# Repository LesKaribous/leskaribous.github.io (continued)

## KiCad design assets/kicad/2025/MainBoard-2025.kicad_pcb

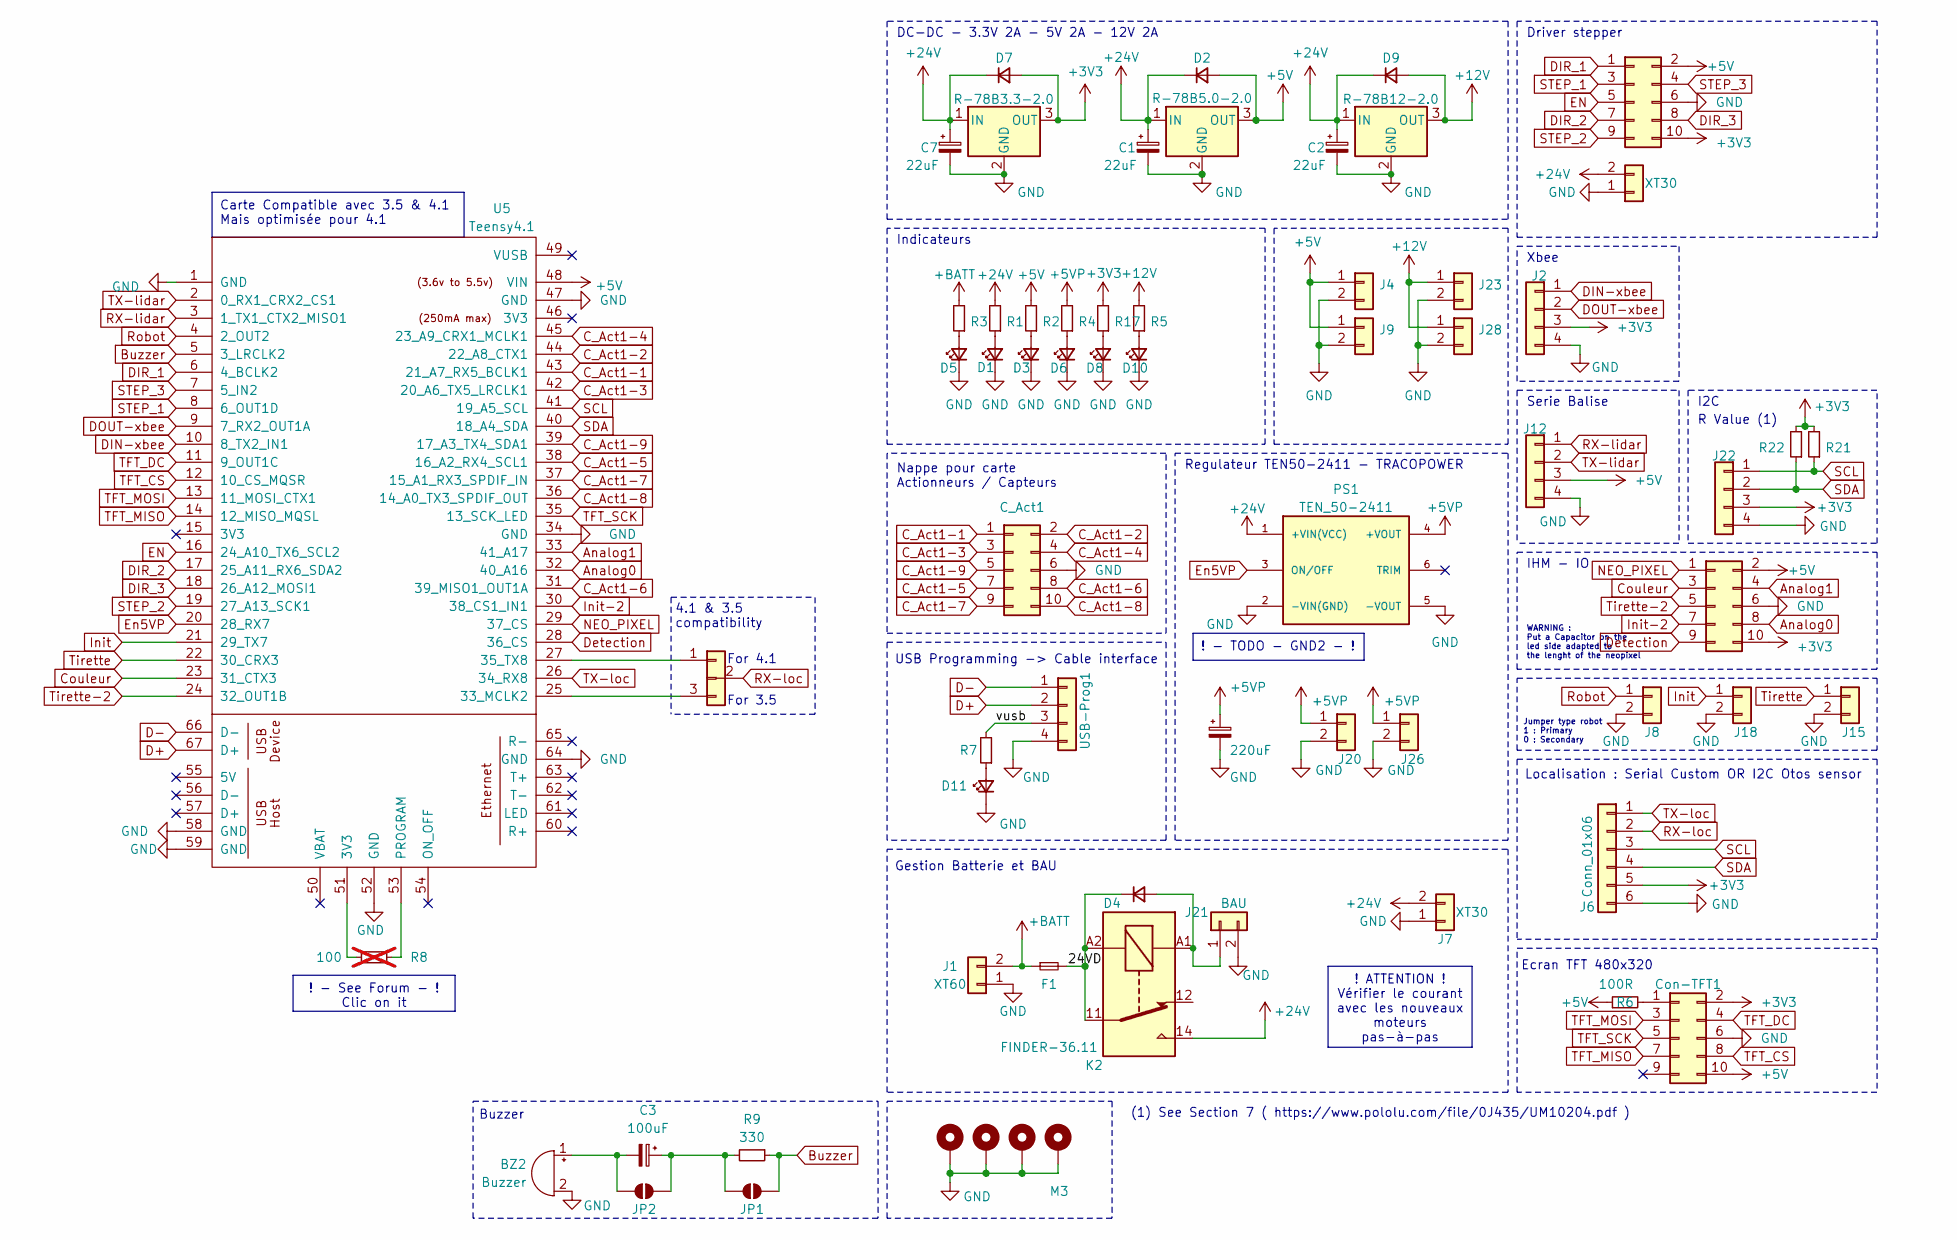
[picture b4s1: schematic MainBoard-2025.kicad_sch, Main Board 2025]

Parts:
BZ2: Buzzer; Buzzer_12x9.5RM7.6
C1, C2, C7: 22uF; CP_Elec_5x5.4
C3: 100uF; CP_Elec_5x5.4
C6: 220uF; CP_Radial_D8.0mm_P3.80mm
C_Act1: Conn_02x05_Odd_Even; IDC-Header_2x05_P2.54mm_Vertical
Con-TFT1: Conn_02x05_Odd_Even; IDC-Header_2x05_P2.54mm_Vertical
D1, D3, D5, D6, D8, D10, D11: LED_Small; LED_1206_3216Metric_Pad1.42x1.75mm_HandSolder
D2, D4, D7, D9: D_Small; D_SMA_Handsoldering
F1: Fuse_Small; Fuseholder_Blade_Mini_Keystone_3568
H1, H2, H3, H4: M3; MountingHole_3.2mm_M3_Pad_Via
IHM-IO1, IHM-IO2: Conn_02x05_Odd_Even; IDC-Header_2x05_P2.54mm_Vertical
J1: XT60; AMASS_XT60-M_1x02_P7.20mm_Vertical
J2, J12, J22: Conn_01x04; Molex_KK-254_AE-6410-04A_1x04_P2.54mm_Vertical
J3: Conn_01x03; PinHeader_1x03_P2.54mm_Vertical
J4, J9, J15, J18, J23, J28: Conn_01x02; Molex_KK-254_AE-6410-02A_1x02_P2.54mm_Vertical
J6: Conn_01x06; Molex_KK-254_AE-6410-06A_1x06_P2.54mm_Vertical
J7, J16: XT30; AMASS_XT30U-F_1x02_P5.0mm_Vertical
J8: Conn_01x02; PinHeader_1x02_P2.54mm_Vertical
J20, J21, J26: BAU; Molex_KK-396_A-41791-0002_1x02_P3.96mm_Vertical
JP1, JP2: SolderJumper_2_Open; SolderJumper-2_P1.3mm_Open_RoundedPad1.0x1.5mm
K2: FINDER-36.11; Relay_SPDT_Finder_36.11
PS1: TEN_50-2411; CONV_TEN_50-2411; PARTREV February 3, 2021
R1, R2, R3, R4, R5, R7, R17, R21, R22: R_Small; R_1206_3216Metric_Pad1.30x1.75mm_HandSolder
R6: 100R; R_1206_3216Metric_Pad1.30x1.75mm_HandSolder
R8: 100; R_1206_3216Metric_Pad1.30x1.75mm_HandSolder; not fitted
R9: 330; R_1206_3216Metric_Pad1.30x1.75mm_HandSolder
U2: R-78B3.3-2.0; Converter_DCDC_RECOM_R-78B-2.0_THT
U3: R-78B12-2.0; Converter_DCDC_RECOM_R-78B-2.0_THT
U4: R-78B5.0-2.0; Converter_DCDC_RECOM_R-78B-2.0_THT
U5: Teensy4.1; Teensy41
USB-Prog1: Conn_01x04; Molex_KK-254_AE-6410-04A_1x04_P2.54mm_Vertical

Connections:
+3V3: Con-TFT1.2, D7.2 (A), IHM-IO1.10, IHM-IO2.10, J2.3, J6.5, J22.3, R17.2, R21.2, R22.2, U2.3 (OUT)
+5V: Con-TFT1.10, D2.2 (A), IHM-IO1.2, IHM-IO2.2, J4.1, J9.1, J12.3, R2.2, R6.1, U4.3 (OUT), U5.48 (VIN)
+5VP: C6.1, J20.1, J26.1, PS1.4 (+VOUT), R4.2
+12V: D9.2 (A), J23.1, J28.1, R5.2, U3.3 (OUT)
+24V: C1.1, C2.1, C7.1, D2.1 (K), D7.1 (K), D9.1 (K), J7.2, J16.2, K2.14, PS1.1 (+VIN(VCC)), R1.2, U2.1 (IN), U3.1 (IN), U4.1 (IN)
+BATT: F1.1, J1.2, R3.2
/24VD: D4.1 (K), F1.2, K2.11, K2.A2
/vusb: R7.2, USB-Prog1.3
Analog0: IHM-IO1.8, U5.32 (40_A16)
Analog1: IHM-IO1.4, U5.33 (41_A17)
Buzzer: JP1.2 (B), R9.1, U5.5 (3_LRCLK2)
C_Act1-1: C_Act1.1, U5.43 (21_A7_RX5_BCLK1)
C_Act1-2: C_Act1.2, U5.44 (22_A8_CTX1)
C_Act1-3: C_Act1.3, U5.42 (20_A6_TX5_LRCLK1)
C_Act1-4: C_Act1.4, U5.45 (23_A9_CRX1_MCLK1)
C_Act1-5: C_Act1.7, U5.38 (16_A2_RX4_SCL1)
C_Act1-6: C_Act1.8, U5.31 (39_MISO1_OUT1A)
C_Act1-7: C_Act1.9, U5.37 (15_A1_RX3_SPDIF_IN)
C_Act1-8: C_Act1.10, U5.36 (14_A0_TX3_SPDIF_OUT)
C_Act1-9: C_Act1.5, U5.39 (17_A3_TX4_SDA1)
Couleur: IHM-IO1.3, U5.23 (31_CTX3)
D+: U5.67 (D+), USB-Prog1.2
D-: U5.66 (D-), USB-Prog1.1
DIN-xbee: J2.1, U5.10 (8_TX2_IN1)
DIR_1: IHM-IO2.1, U5.6 (4_BCLK2)
DIR_2: IHM-IO2.7, U5.17 (25_A11_RX6_SDA2)
DIR_3: IHM-IO2.8, U5.18 (26_A12_MOSI1)
DOUT-xbee: J2.2, U5.9 (7_RX2_OUT1A)
Detection: IHM-IO1.9, U5.28 (36_CS)
EN: IHM-IO2.5, U5.16 (24_A10_TX6_SCL2)
En5VP: PS1.3 (ON/OFF), U5.20 (28_RX7)
GND: BZ2.2 (-), C1.2, C2.2, C6.2, C7.2, C_Act1.6, Con-TFT1.6, D1.1 (K), D3.1 (K), D5.1 (K), D6.1 (K), D8.1 (K), D10.1 (K), D11.1 (K), H1.1, H2.1, H3.1, H4.1, IHM-IO1.6, IHM-IO2.6, J1.1, J2.4, J4.2, J6.6, J7.1, J8.2, J9.2, J12.4, J15.2, J16.1, J18.2, J20.2, J21.2, J22.4, J23.2, J26.2, J28.2, PS1.2 (-VIN(GND)), PS1.5 (-VOUT), U2.2 (GND), U3.2 (GND), U4.2 (GND), U5.1 (GND), U5.34 (GND), U5.47 (GND), U5.52 (GND), U5.58 (GND), U5.59 (GND), U5.64 (GND), USB-Prog1.4
Init: J18.1, U5.21 (29_TX7)
Init-2: IHM-IO1.7, U5.30 (38_CS1_IN1)
NEO_PIXEL: IHM-IO1.1, U5.29 (37_CS)
unnamed: BZ2.1 (+), C3.2, JP2.1 (A)
unnamed: Con-TFT1.1, R6.2
unnamed: D1.2 (A), R1.1
unnamed: D3.2 (A), R2.1
unnamed: D4.2 (A), J21.1, K2.A1
unnamed: D5.2 (A), R3.1
unnamed: D6.2 (A), R4.1
unnamed: D8.2 (A), R17.1
unnamed: D10.2 (A), R5.1
unnamed: D11.2 (A), R7.1
unnamed: J3.1, U5.27 (35_TX8)
unnamed: J3.3, U5.25 (33_MCLK2)
unnamed: C3.1, JP1.1 (A), JP2.2 (B), R9.2
unnamed: R8.2, U5.51 (3V3)
unnamed: R8.1, U5.53 (PROGRAM)
RX-lidar: J12.1, U5.3 (1_TX1_CTX2_MISO1)
RX-loc: J3.2, J6.2
Robot: J8.1, U5.4 (2_OUT2)
SCL: J6.3, J22.1, R21.1, U5.41 (19_A5_SCL)
SDA: J6.4, J22.2, R22.1, U5.40 (18_A4_SDA)
STEP_1: IHM-IO2.3, U5.8 (6_OUT1D)
STEP_2: IHM-IO2.9, U5.19 (27_A13_SCK1)
STEP_3: IHM-IO2.4, U5.7 (5_IN2)
TFT_CS: Con-TFT1.8, U5.12 (10_CS_MQSR)
TFT_DC: Con-TFT1.4, U5.11 (9_OUT1C)
TFT_MISO: Con-TFT1.7, U5.14 (12_MISO_MQSL)
TFT_MOSI: Con-TFT1.3, U5.13 (11_MOSI_CTX1)
TFT_SCK: Con-TFT1.5, U5.35 (13_SCK_LED)
TX-lidar: J12.2, U5.2 (0_RX1_CRX2_CS1)
TX-loc: J6.1, U5.26 (34_RX8)
Tirette: J15.1, U5.22 (30_CRX3)
Tirette-2: IHM-IO1.5, U5.24 (32_OUT1B)

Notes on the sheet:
Carte Compatible avec 3.5 & 4.1 Mais optimisée pour 4.1
! - See Forum - ! Clic on it
! ATTENTION ! Vérifier le courant avec les nouveaux moteurs pas-à-pas
! - TODO - GND2 - !
Localisation : Serial Custom OR I2C Otos sensor
USB Programming -> Cable interface
Nappe pour carte Actionneurs / Capteurs
Gestion Batterie et BAU
WARNING : Put a Capacitor on the led side adapted to the lenght of the neopixel
For 4.1
4.1 & 3.5 compatibility
(1) See Section 7 ( https://www.pololu.com/file/0J435/UM10204.pdf )
Serie Balise
Buzzer
Jumper type robot 1 : Primary 0 : Secondary
Driver stepper
Xbee
Ecran TFT 480x320
DC-DC - 3.3V 2A - 5V 2A - 12V 2A
For 3.5
R Value (1)
Regulateur TEN50-2411 - TRACOPOWER
Indicateurs
IHM - IO
I2C

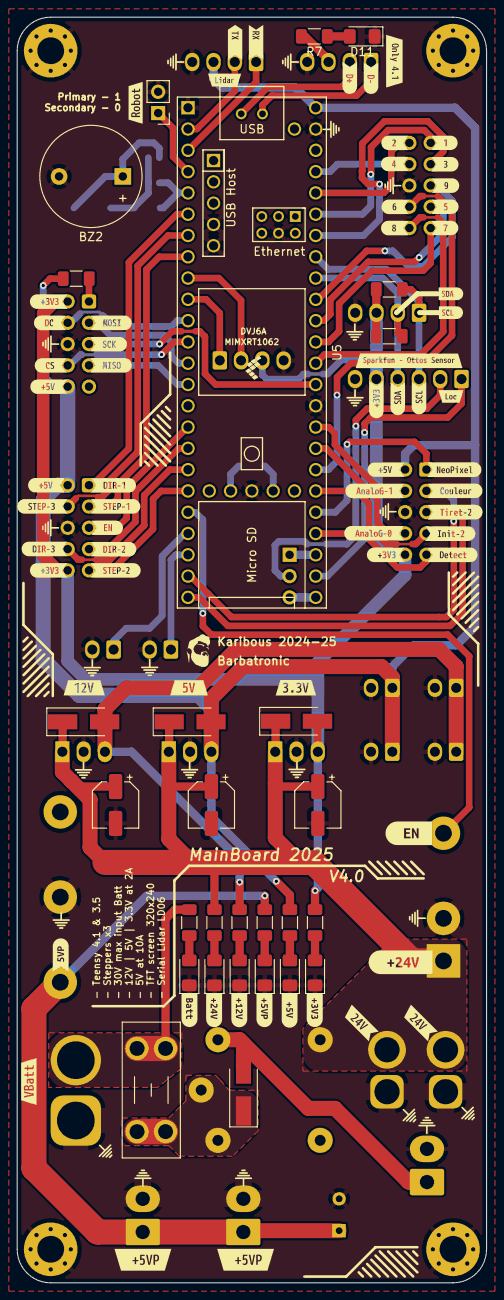
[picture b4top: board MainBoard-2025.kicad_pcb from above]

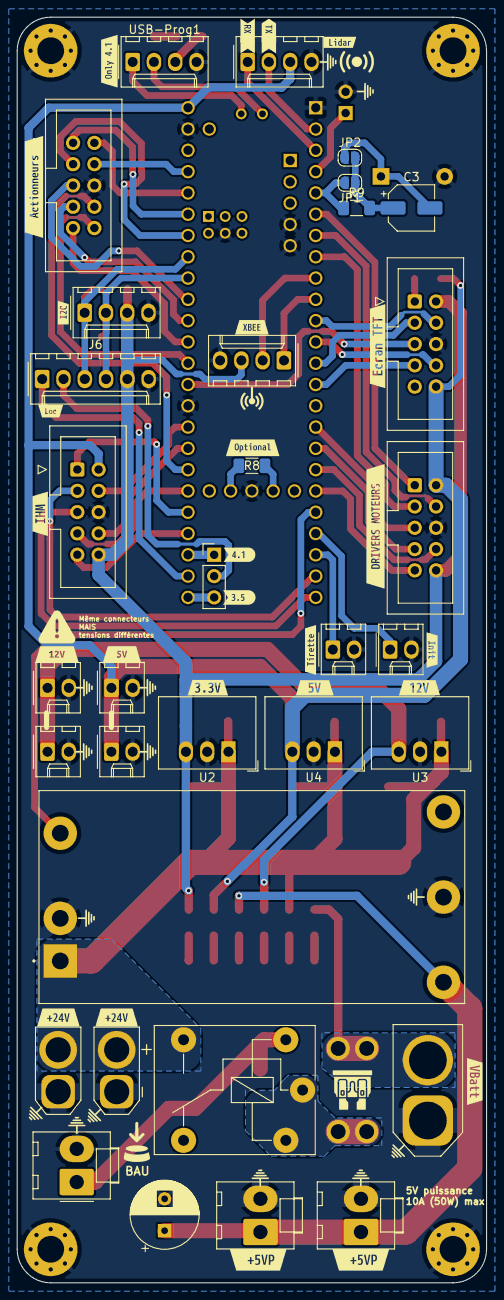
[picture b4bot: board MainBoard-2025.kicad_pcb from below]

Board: 2 copper layers, 56.0 x 151.0 mm, 156 parts (59 on the bottom side), 67 nets.

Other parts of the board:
kibuzzard-670C2FEC, kibuzzard-670C2FEC#2: G***; kibuzzard-670C2FEC
kibuzzard-670C2FF9, kibuzzard-670C2FF9#2: G***; kibuzzard-670C2FF9
kibuzzard-670C3A1A: G***; kibuzzard-670C3A1A
kibuzzard-670C3EA9: G***; kibuzzard-670C3EA9
kibuzzard-670C3EB4: G***; kibuzzard-670C3EB4
kibuzzard-670C3F16: G***; kibuzzard-670C3F16
kibuzzard-670C31DA: G***; kibuzzard-670C31DA
kibuzzard-670C31EF: G***; kibuzzard-670C31EF
kibuzzard-670C33A6, kibuzzard-670C33A6#2, kibuzzard-670C33A6#3, kibuzzard-670C33A6#4: G***; kibuzzard-670C33A6
kibuzzard-670C34D3, kibuzzard-670C34D3#2, kibuzzard-670C34D3#3, kibuzzard-670C34D3#4: G***; kibuzzard-670C34D3
kibuzzard-670C34F5, kibuzzard-670C34F5#2, kibuzzard-670C34F5#3: G***; kibuzzard-670C34F5
kibuzzard-670C35E1: G***; kibuzzard-670C35E1
kibuzzard-670C35E9: G***; kibuzzard-670C35E9
kibuzzard-670C35F6: G***; kibuzzard-670C35F6
kibuzzard-670C35FE: G***; kibuzzard-670C35FE
kibuzzard-670C36A0: G***; kibuzzard-670C36A0
kibuzzard-670C36A7: G***; kibuzzard-670C36A7
kibuzzard-670C36BE: G***; kibuzzard-670C36BE
kibuzzard-670C36EB: G***; kibuzzard-670C36EB
kibuzzard-670C36F4: G***; kibuzzard-670C36F4
kibuzzard-670C37A2: G***; kibuzzard-670C37A2
kibuzzard-670C37B4: G***; kibuzzard-670C37B4
kibuzzard-670C37B9: G***; kibuzzard-670C37B9
kibuzzard-670C37C6: G***; kibuzzard-670C37C6
kibuzzard-670C37D3: G***; kibuzzard-670C37D3
kibuzzard-670C37D7: G***; kibuzzard-670C37D7
kibuzzard-670C37DD: G***; kibuzzard-670C37DD
kibuzzard-670C37E0: G***; kibuzzard-670C37E0
kibuzzard-670C38D3: G***; kibuzzard-670C38D3
kibuzzard-670C38FC: G***; kibuzzard-670C38FC
kibuzzard-670C323B: G***; kibuzzard-670C323B
kibuzzard-670C334A: G***; kibuzzard-670C334A
kibuzzard-670C345D: G***; kibuzzard-670C345D
kibuzzard-670C355C: G***; kibuzzard-670C355C
kibuzzard-670C356A: G***; kibuzzard-670C356A
kibuzzard-670C364B: G***; kibuzzard-670C364B
kibuzzard-670C368F: G***; kibuzzard-670C368F
kibuzzard-670C375F: G***; kibuzzard-670C375F
kibuzzard-670C379B: G***; kibuzzard-670C379B
kibuzzard-670C381F: G***; kibuzzard-670C381F
kibuzzard-670C3111: G***; kibuzzard-670C3111
kibuzzard-670C3244: G***; kibuzzard-670C3244
kibuzzard-670C3331: G***; kibuzzard-670C3331
kibuzzard-670C3352: G***; kibuzzard-670C3352
kibuzzard-670C3359: G***; kibuzzard-670C3359
kibuzzard-670C3379: G***; kibuzzard-670C3379
kibuzzard-670C3380: G***; kibuzzard-670C3380
kibuzzard-670C3411, kibuzzard-670C3411#2: G***; kibuzzard-670C3411
kibuzzard-670C3554: G***; kibuzzard-670C3554
kibuzzard-670C3560: G***; kibuzzard-670C3560
kibuzzard-670C3565: G***; kibuzzard-670C3565
kibuzzard-670C3571: G***; kibuzzard-670C3571
kibuzzard-670C3577: G***; kibuzzard-670C3577
kibuzzard-670C3605: G***; kibuzzard-670C3605
kibuzzard-670C3646: G***; kibuzzard-670C3646
kibuzzard-670C3688: G***; kibuzzard-670C3688
kibuzzard-670C3826: G***; kibuzzard-670C3826
kibuzzard-670C3843: G***; kibuzzard-670C3843
kibuzzard-670C3846: G***; kibuzzard-670C3846
kibuzzard-670C3872: G***; kibuzzard-670C3872
kibuzzard-670C3891, kibuzzard-670C3891#2: G***; kibuzzard-670C3891
kibuzzard-670C3904: G***; kibuzzard-670C3904
kibuzzard-6493EE9E: G***; kibuzzard-6493EE9E
kibuzzard-6493EEAC: G***; kibuzzard-6493EEAC
kibuzzard-6493F0A8: G***; kibuzzard-6493F0A8
kibuzzard-6493F0E7: G***; kibuzzard-6493F0E7
kibuzzard-6493F09E: G***; kibuzzard-6493F09E
kibuzzard-6493F100: G***; kibuzzard-6493F100
kibuzzard-64944D37, kibuzzard-64944D37#2: G***; kibuzzard-64944D37
kibuzzard-649443DA, kibuzzard-649443DA#2: G***; kibuzzard-649443DA
kibuzzard-6494437E, kibuzzard-6494437E#2: G***; kibuzzard-6494437E
kibuzzard-6494443F: G***; kibuzzard-6494443F
kibuzzard-64944345, kibuzzard-64944345#2: G***; kibuzzard-64944345
kibuzzard-64944398, kibuzzard-64944398#2: G***; kibuzzard-64944398

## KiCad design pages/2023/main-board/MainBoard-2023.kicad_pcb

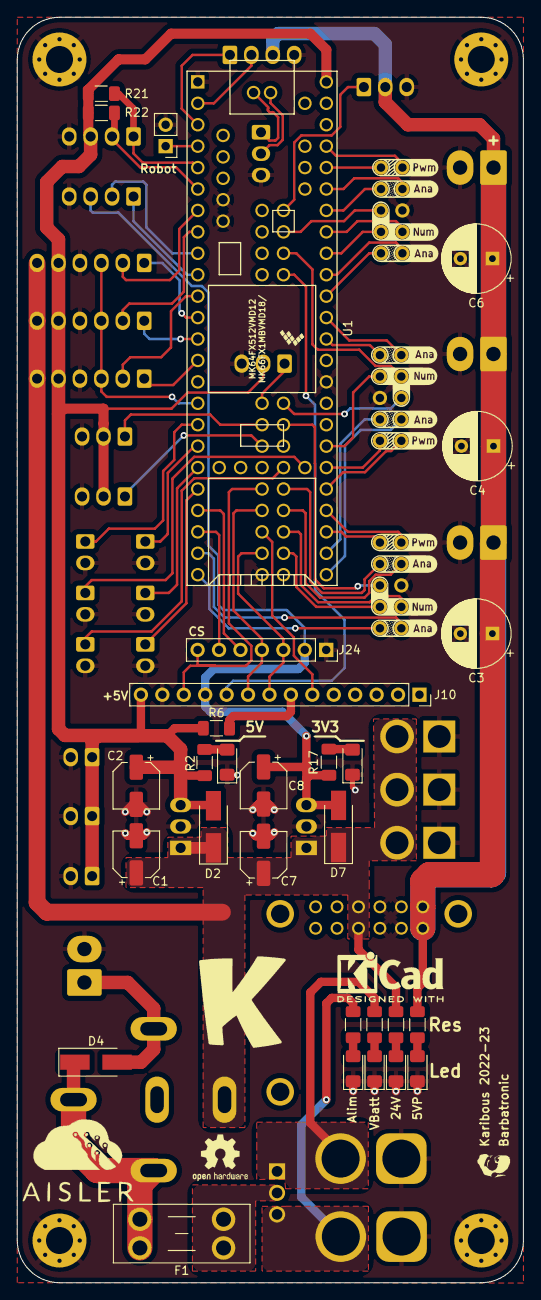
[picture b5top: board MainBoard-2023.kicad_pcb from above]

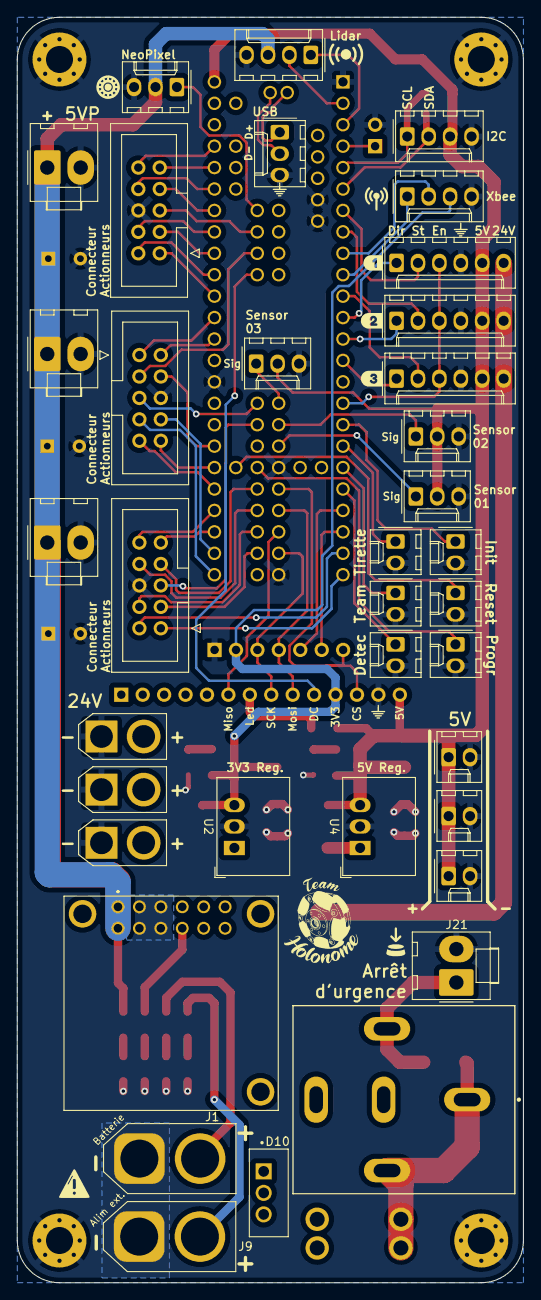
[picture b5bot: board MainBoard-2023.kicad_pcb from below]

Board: 2 copper layers, 60.0 x 150.0 mm, 74 parts (40 on the bottom side), 77 nets.

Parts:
C1, C2, C7, C8: CP_Small; CP_Elec_5x5.4
C3, C4, C6: 220uF; CP_Radial_D8.0mm_P3.80mm
C_Act1, C_Act2, C_Act3: Conn_02x05_Odd_Even; IDC-Header_2x05_P2.54mm_Vertical
D1, D3, D5, D6, D8, D9: LED_Small; LED_1206_3216Metric_Pad1.42x1.75mm_HandSolder
D2, D4, D7: D_Small; D_SMA_Handsoldering
D10: D_Dual_CommonCathode_AKA_Parallel; BYV34-400
F1: Fuse_Small; Fuseholder_Blade_Mini_Keystone_3568
H1, H2, H3, H4: M3; MountingHole_3.2mm_M3_Pad_Via
J1, J9: XT60; AMASS_XT60-M_1x02_P7.20mm_Vertical
J2, J12, J22: Conn_01x04; Molex_KK-254_AE-6410-04A_1x04_P2.54mm_Vertical
J3, J5, J6: ConStep1; Molex_KK-254_AE-6410-06A_1x06_P2.54mm_Vertical
J4, J23, J28, J29, J32, J37, J38, J39, J40: Conn_01x02; Molex_KK-254_AE-6410-02A_1x02_P2.54mm_Vertical
J7, J16, J17: XT30; AMASS_XT30U-F_1x02_P5.0mm_Vertical
J8: Conn_01x02; PinHeader_1x02_P2.54mm_Vertical
J10: Conn_01x14; PinSocket_1x14_P2.54mm_Vertical
J11, J13, J14, J15, J30: Conn_01x03; Molex_KK-254_AE-6410-03A_1x03_P2.54mm_Vertical
J20, J21, J26, J27: BAU; Molex_KK-396_A-41791-0002_1x02_P3.96mm_Vertical
J24: Conn_01x07; PinSocket_1x07_P2.54mm_Vertical
K1: CB1-P-24V; Panasonic_Electric_Works-CB1-P-24V-MFG
PS1: D36V50F5
R1, R2, R3, R4, R5, R6, R17, R21, R22: R_Small; R_1206_3216Metric_Pad1.30x1.75mm_HandSolder
U1: Teensy3.5_All_Pins; Teensy35_36_All_Pins
U2: R-78B3.3-2.0; Converter_DCDC_RECOM_R-78B-2.0_THT
U4: R-78B5.0-2.0; Converter_DCDC_RECOM_R-78B-2.0_THT
kibuzzard-62E65D6B: G***; kibuzzard-62E65D6B
kibuzzard-62E65D7D: G***; kibuzzard-62E65D7D
kibuzzard-62E65D77: G***; kibuzzard-62E65D77

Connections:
+3V3: C8.1, D7.2 (A), J2.3, J10.11, J24.2, R17.2, U2.3 (OUT)
+5V: C2.1, D2.2 (A), J3.5, J5.5, J6.5, J10.14, J11.2, J13.2, J14.2, J22.3, J23.1, J28.1, J29.1, R2.2, R6.1, R21.2, R22.2, U1.53 (Vin), U4.3 (OUT)
+5VP: C3.1, C4.1, C6.1, J12.3, J20.1, J26.1, J27.1, J30.2, PS1.1 (VOUT_1), PS1.2 (VOUT_2), R4.2
+24V: C1.1, C7.1, D2.1 (K), D7.1 (K), J3.6, J5.6, J6.6, J7.2, J16.2, J17.2, K1.87, PS1.7 (VIN_1), PS1.8 (VIN_2), R1.2, U2.1 (IN), U4.1 (IN)
+BATT: D10.1 (K), J1.2, R3.2
/24VD: D10.2 (A), F1.1
/D+: J15.1, U1.88 (D+)
/D-: J15.2, U1.87 (D-)
ALIM: D10.3 (K), J9.2, R5.2
CS: J10.12, J24.7, U1.70 (43_CS2)
C_Act1-1: C_Act1.1, U1.43 (16_A2_SCL0_Touch)
C_Act1-2: C_Act1.2, U1.44 (17_A3_SDA0_Touch)
C_Act1-3: C_Act1.3, U1.45 (18_A4_SDA0_Touch)
C_Act1-4: C_Act1.4, U1.46 (19_A5_SCL0_Touch)
C_Act1-5: C_Act1.7, U1.47 (20_A6_PWM_CS0_SCK1)
C_Act1-6: C_Act1.8, U1.48 (21_A7_PWM_CS0_MOSI1)
C_Act1-7: C_Act1.9, U1.49 (22_A8_PWM_Touch)
C_Act1-8: C_Act1.10, U1.50 (23_A9_PWM_Touch)
C_Act1-9: C_Act1.5, U1.85 (56)
C_Act2-1: C_Act2.10, U1.35 (38_A19_PWM_SDA1)
C_Act2-2: C_Act2.9, U1.34 (37_A18_PWM_SCL1)
C_Act2-3: C_Act2.8, U1.31 (34_A15_RX5_CAN1RX_SDA0)
C_Act2-4: C_Act2.7, U1.30 (33_A14_TX5_CAN1TX_SCL0)
C_Act2-5: C_Act2.4, U1.36 (39_A20)
C_Act2-6: C_Act2.3, U1.84 (55)
C_Act2-7: C_Act2.2, U1.41 (14_A0_PWM_SCK0)
C_Act2-8: C_Act2.1, U1.42 (15_A1_CS0_Touch)
C_Act2-9: C_Act2.5, U1.82 (53_SCK2)
C_Act3-1: C_Act3.1, U1.24 (32_A13_TX4_SCK1)
C_Act3-2: C_Act3.2, U1.23 (31_A12_RX4_CS1)
C_Act3-3: C_Act3.3, U1.76 (47_RX6_SCL0)
C_Act3-4: C_Act3.4, U1.77 (48_TX6_SDA0)
C_Act3-5: C_Act3.7, U1.79 (50_A24)
C_Act3-6: C_Act3.8, U1.78 (49_A23)
C_Act3-7: C_Act3.9, U1.32 (35_A16_PWM)
C_Act3-8: C_Act3.10, U1.33 (36_A17_PWM)
C_Act3-9: C_Act3.5, U1.81 (52_MOSI2)
Couleur: J37.1, U1.19 (27_RX1_SCK0)
DC: J24.6, U1.22 (30_PWM_CAN0RX_Touch)
DIN-xbee: J2.1, U1.10 (8_TX3_MISO0_SDA0)
DIR_1: J5.1, U1.12 (10_PWM_TX2_CS0)
DIR_2: J3.1, U1.13 (11_MOSI0)
DIR_3: J6.1, U1.14 (12_MISO0)
DOUT-xbee: J2.2, U1.9 (7_RX3_MOSI0_SCL0)
Detection: J38.1, U1.20 (28_MOSI0)
EN: J3.3, J5.3, J6.3, U1.16 (24)
GND: C1.2, C2.2, C3.2, C4.2, C6.2, C7.2, C8.2, C_Act1.6, C_Act2.6, C_Act3.6, D1.1 (K), D3.1 (K), D5.1 (K), D6.1 (K), D8.1 (K), D9.1 (K), H1.1, H2.1, H3.1, H4.1, J1.1, J2.4, J3.4, J4.2, J5.4, J6.4, J7.1, J8.2, J9.1, J10.13, J11.3, J12.4, J13.3, J14.3, J15.3, J16.1, J17.1, J20.2, J21.2, J22.4, J23.2, J24.1, J26.2, J27.2, J28.2, J29.2, J30.3, J32.2, J37.2, J38.2, J39.2, J40.2, PS1.3 (GND_1), PS1.4 (GND_2), PS1.5 (GND_3), PS1.6 (GND_4), U1.1 (GND), U1.27 (GND), U1.39 (GND), U1.61 (GND), U1.62 (GND), U1.74 (GND), U2.2 (GND), U4.2 (GND)
Init: J4.1, U1.17 (25)
MOSI: J10.9, J24.4, U1.71 (44_MOSI2)
NEO_PIXEL: J30.1, U1.86 (57)
unnamed: D1.2 (A), R1.1
unnamed: D3.2 (A), R2.1
unnamed: D4.1 (K), F1.2, K1.30, K1.85
unnamed: D4.2 (A), J21.1, K1.86
unnamed: D5.2 (A), R3.1
unnamed: D6.2 (A), R4.1
unnamed: D8.2 (A), R17.1
unnamed: D9.2 (A), R5.1
unnamed: J10.7, R6.2
Program: J39.1, U1.28 (Program)
RES: J24.5, U1.21 (29_PWM_CAN0TX_Touch)
RX-lidar: J12.1, U1.3 (1_TX1_MISO1_Touch)
Reset: J40.1, U1.29 (Reset)
Robot: J8.1, U1.4 (2_PWM)
SCK: J10.8, J24.3, U1.73 (46_SCK2)
SCL: J22.1, R21.1, U1.5 (3_PWM_CAN0TX_SCL2)
SDA: J22.2, R22.1, U1.6 (4_PWM_CAN0RX_SDA2)
STEP_1: J5.2, U1.7 (5_PWM_TX1_MISO1)
STEP_2: J3.2, U1.8 (6_PWM)
STEP_3: J6.2, U1.11 (9_PWM_RX2_CS0)
Sensor-01: J11.1, U1.69 (42)
Sensor-02: J13.1, U1.68 (41)
Sensor-03: J14.1, U1.67 (40)
TFT_DC: J10.10, U1.83 (54_CS2)
TFT_MISO: J10.6, U1.72 (45_MISO2)
TX-lidar: J12.2, U1.2 (0_RX1_MOSI1_Touch)
Tirette: J32.1, U1.18 (26_TX1_SCL2)

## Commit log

2022-08-21 change url
2022-08-21 change gemfile platform
2022-08-21 restore
2022-08-21 test
2022-08-26 add sponsorship page and data
2022-08-27 add robot
2022-08-28 add robots pages functionnalities
2022-08-28 change tags pages behaviour
2022-08-28 move tags
2022-08-28 fix underline border for icons and image (robots)
2022-08-28 fix constant heigh of the cards
2022-08-28 try jumbotron
2022-08-28 add content
    - add content for about and barbatronic
    - add caroussel
    - issue with TOC -> To fix
2022-08-30 Create 2022-08-26-PCB
2022-08-30 change extension
2022-08-30 add image to post
2022-08-30 nouveaux posts
2022-11-06 add project radiocommande
2022-12-18 test 3d model-viewer
2022-12-18 add style
2022-12-27 adapt for model-viewer
2022-12-27 test chemin
2022-12-27 fix link
2022-12-27 test image link
2022-12-27 test pages directories
2022-12-27 add permalink: pretty
2022-12-27 correct doc visualisation
2022-12-28 update version
2022-12-28 fix toc issue on the pages
2022-12-28 [Automation] Site update No.27
2023-07-23 update robots and sponsors
2023-07-23 create mainboard page with pinion
2023-07-26 refactor robot page
2023-07-26 fix broken links
2023-07-29 add include liquid and doc
2023-07-29 refactor with medi instead of card
2023-07-29 add page
2023-07-29 update modal to display results
2023-07-29 add modal points detail
2023-07-30 add ':' to sanitized title
2023-07-30 add content to serie 1
2023-07-31 fix image display
2023-08-02 update description
2023-08-02 change pages by post
2023-08-10 update blog posts
2023-08-10 add posts
2023-08-11 new posts
2023-08-11 fix link error
2023-08-11 fix error link
2023-08-11 fix typo
2023-08-11 add jumbotron on the homing page
2023-08-11 fix toast header
2023-08-11 try fixing update toast
2023-08-11 change baseurl
2023-08-11 add shop on sidebar and custom redirection on tabs
2023-08-11 add hide parameters to tabs
2023-08-11 add live countdown
2023-08-13 New doc
2023-08-15 Brouillon de post
2023-08-16 add new post
2023-08-16 update images and title
2023-08-16 update content and fix typo
2023-08-18 update and refactor doc
2023-08-18 refactor docs folders and generation
2023-09-02 new post
2023-09-02 fix popup notification
2023-09-02 move notification popup
2023-09-02 update jumbotron
2023-09-27 fix links
2023-10-15 update sponsors
2023-10-15 New post beta 2024
2023-11-12 test kiCanvas
2023-11-12 add to assets
2024-01-02 new and update sponsors
2024-01-02 new updated post
2024-01-02 [Automation] Site update No.71
2024-04-12 update script ModelViewer
2024-04-15 add PCB
2024-04-15 nouveaux post
2024-04-15 add date sponsor
2024-04-15 fix date
2024-04-22 WIP - gallery Belgium 2024
2024-04-22 wip: new gallery
2024-04-22 fix: carrousel is now in gallery
2024-04-22 add modal to galleyr
2024-04-22 fix : posts name
2024-04-22 change ruby version
2024-04-22 chnage ruby version to 3.1.0
2024-04-22 resolve gemfile
2024-04-22 change jekyll-sass-converter version
2024-04-22 add bundler update
2024-04-22 revert version
2024-04-22 change alt attribute
2024-04-22 WIP - change post date
2024-04-27 add sponsors
2024-04-27 fix score
2024-05-13 update doc
2024-05-25 import images
2024-05-25 add gallery
2024-05-25 add gallery cdr 2024
2024-05-25 brouillon post cdr 2024
2024-05-25 update timestamp
2024-05-25 publish wip post
2024-05-31 add connectors ans battery - for 1A robot
2024-05-31 add BAU link
2024-05-31 add bottom entry socket
2024-05-31 change link
2024-06-01 add absolute sensor
2024-06-01 update news
2024-06-01 [Automation] Site update No.108
2024-10-22 new post for CDR 2025
2024-10-22 [Automation] Site update No.110
2024-10-29 New post + fix typo
2024-11-03 MAJ KiCanvas - Add PCB docs
2024-11-05 update link to shop
2024-11-17 New post RS
2024-11-17 change date
2024-12-02 add new page for PAMI
2024-12-02 [Automation] Site update No.117
2025-01-16 merci aisler
2025-01-16 new galleries
2025-01-16 fix name
2025-01-16 typo
2025-04-25 fix folder
2025-04-25 change image ratio
2025-04-25 [Automation] Site update No.124
2025-06-08 add gallery CDR 2025
2025-06-08 change image format
2025-06-10 fix target
2025-06-10 fix gem
2025-06-11 fix jumbotron and new post
2025-06-11 [Automation] Site update No.134
2025-06-29 add giscus for comments
2025-06-29 add id an category
2025-06-29 Fix type
2025-06-29 update tail navigation
2025-06-29 [Automation] Site update No.138
